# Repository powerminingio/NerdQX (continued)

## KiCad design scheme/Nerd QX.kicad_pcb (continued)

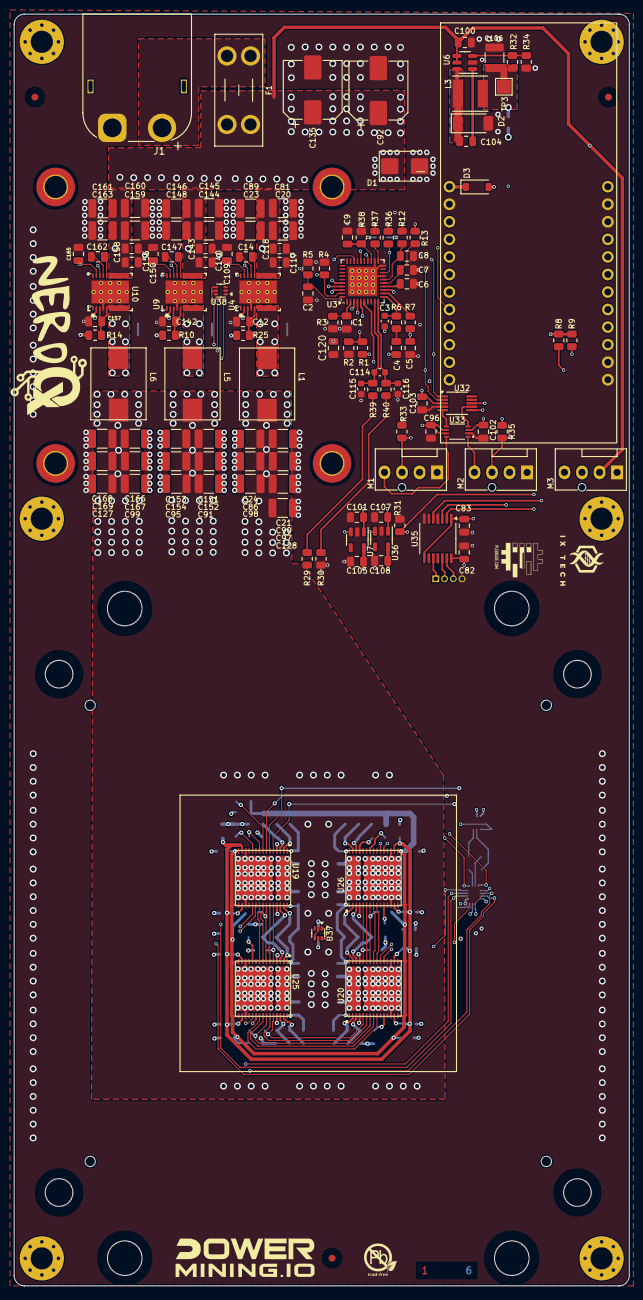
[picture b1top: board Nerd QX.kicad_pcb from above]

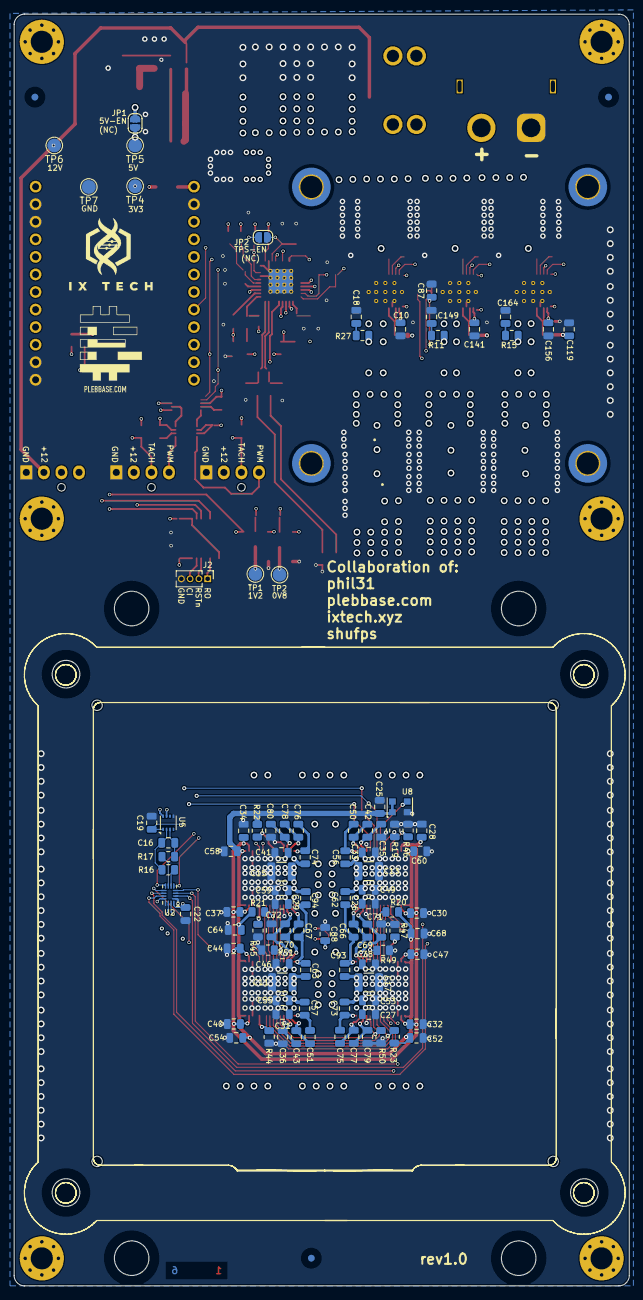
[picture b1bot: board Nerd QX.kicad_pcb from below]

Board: 6 copper layers, 89.0 x 184.0 mm, 237 parts (101 on the bottom side), 122 nets.

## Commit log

2025-09-05 Add LICENSE
2025-09-05 Add .gitignore
2025-09-06 Add STEP file for NerdQX
2025-09-06 PCB dimensions plan added
2025-09-06 KiCad project data added for NerdQX
    ... The first revision of the NerdQX, following the successful testing of the first prototype. This basis provides the opportunity to manufacture the second prototype and thus later move into the pro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
2025-09-06 Add gerbers files
2025-09-06 Added bom for NerdQX
2025-09-06 Image data added as asset
2025-09-06 changelog.md added
    ... for logging the changes of each revision
2025-09-06 README.md added
2025-10-01 silkscreen update for prototype boards
2025-10-13 Copy fix in README.md
2025-10-13 Latest lead photo inserted
2025-10-13 CHANGELOG updated for revision 1.0
2025-10-13 NerdQX ORIGINAL Initiative information added
2025-10-13 case sensitive
2025-10-13 Case sensitive CHANGELOG fix
2025-11-16 Updated schematics with correct cap rating
    We upgraded certain capacitors to a higher nF rating and have changed the schematic to reflect it so the BOM can be generated accurately.
2025-11-16 Gerber files exported and verified
2025-11-16 BOM updated according to current schematics
2025-12-19 Powermining logo added. USA flag removed
2026-01-16 Moved J1 XT60 connector from top to bottom side of the board. Exported new gerber files, drill files and P&P files. Exported new PCB STEP file.
2026-01-16 Revert "Moved J1 XT60 connector from top to bottom side of the board. Exported new gerber files, drill files and P&P files. Exported new PCB STEP file."
    This reverts commit 3dc59e0cc8feb32dc6b1378662933946a2f0176a.
